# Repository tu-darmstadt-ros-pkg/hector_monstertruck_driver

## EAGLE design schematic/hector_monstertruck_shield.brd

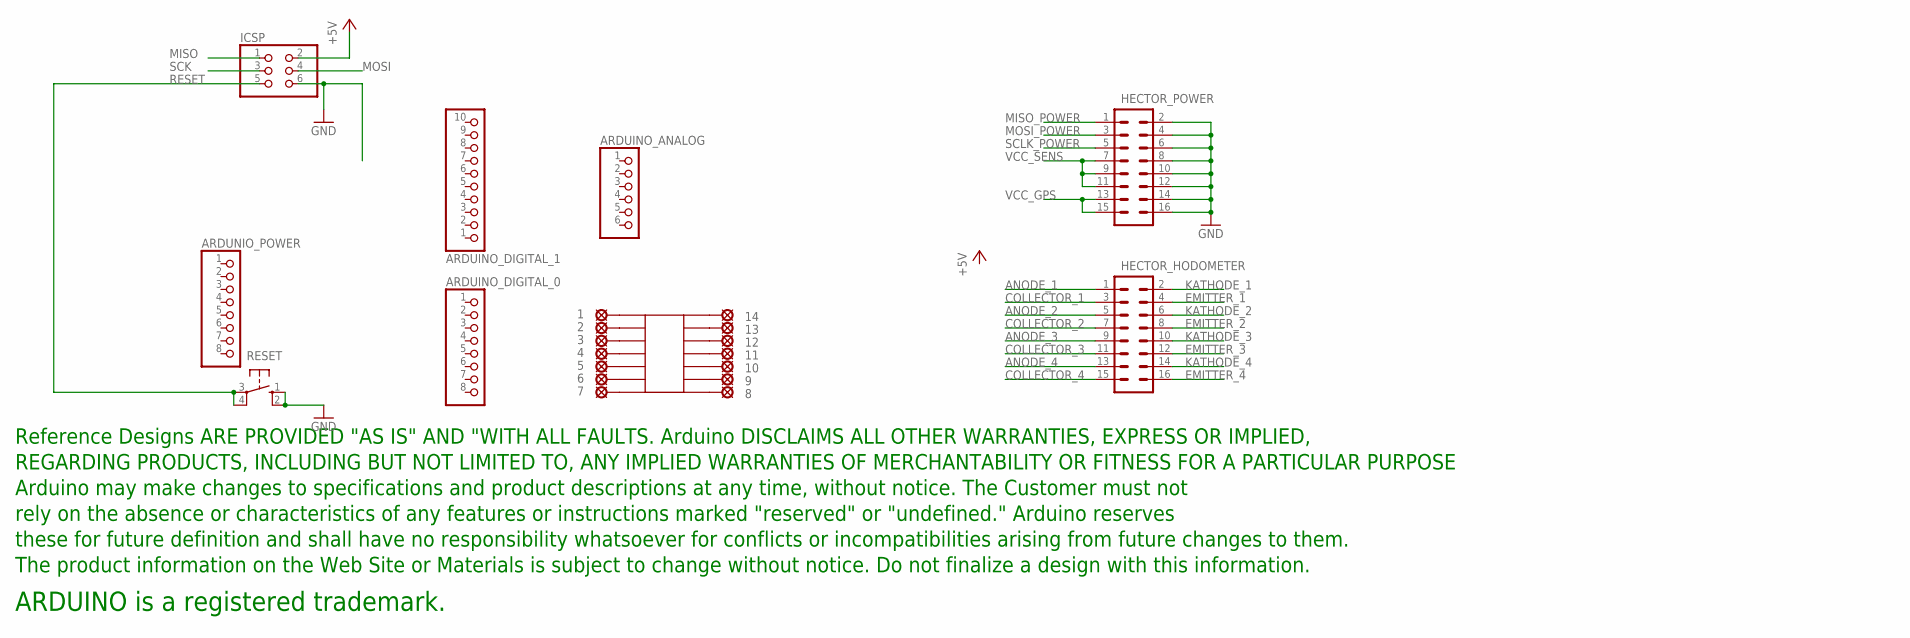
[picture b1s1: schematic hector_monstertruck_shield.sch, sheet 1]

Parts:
1, 2, 3, 4, 5, 6, 7, 8, 9, 10, 11, 12, 13, 14: LSP10
ARDUINO_ANALOG: PINHD-1X6; 1X06
ARDUINO_DIGITAL_0: PINHD-1X8TH; 1X08-TH
ARDUINO_DIGITAL_1: PINHD-1X10TH; 1X10-TH
ARDUNIO_POWER: PINHD-1X8TH; 1X08-TH
HECTOR_HODOMETER: M08X2; 2X8
HECTOR_POWER: M08X2; 2X8
IC2: SMD-14; SO-14NMW
ICSP: PINHD-2X3; 2X03
RESET: 10-XX; B3F-10XX
U$1: DISCLAIMER

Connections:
+5V: ICSP.2; also elsewhere on the board
ANODE_1: HECTOR_HODOMETER.1
ANODE_2: HECTOR_HODOMETER.5
ANODE_3: HECTOR_HODOMETER.9
ANODE_4: HECTOR_HODOMETER.13
COLLECTOR_1: HECTOR_HODOMETER.3
COLLECTOR_2: HECTOR_HODOMETER.7
COLLECTOR_3: HECTOR_HODOMETER.11
COLLECTOR_4: HECTOR_HODOMETER.15
EMITTER_1: HECTOR_HODOMETER.4
EMITTER_2: HECTOR_HODOMETER.8
EMITTER_3: HECTOR_HODOMETER.12
EMITTER_4: HECTOR_HODOMETER.16
GND: HECTOR_POWER.2, HECTOR_POWER.4, HECTOR_POWER.6, HECTOR_POWER.8, HECTOR_POWER.10, HECTOR_POWER.12, HECTOR_POWER.14, HECTOR_POWER.16, ICSP.6, RESET.1 (S), RESET.2 (S1); also elsewhere on the board
KATHODE_1: HECTOR_HODOMETER.2
KATHODE_2: HECTOR_HODOMETER.6
KATHODE_3: HECTOR_HODOMETER.10
KATHODE_4: HECTOR_HODOMETER.14
MISO: ICSP.1
MISO_POWER: HECTOR_POWER.1
MOSI: ICSP.4
MOSI_POWER: HECTOR_POWER.3
unnamed: 14.MP, IC2.P$14
unnamed: 13.MP, IC2.P$13
unnamed: 12.MP, IC2.P$12
unnamed: 11.MP, IC2.P$11
unnamed: 10.MP, IC2.P$10
unnamed: 9.MP, IC2.P$9
unnamed: 8.MP, IC2.P$8
unnamed: 7.MP, IC2.P$7
unnamed: 6.MP, IC2.P$6
unnamed: 5.MP, IC2.P$5
unnamed: 3.MP, IC2.P$3
unnamed: 2.MP, IC2.P$2
unnamed: 1.MP, IC2.P$1
unnamed: 4.MP, IC2.P$4
RESET: ICSP.5, RESET.3, RESET.4 (P1)
SCK: ICSP.3
SCLK_POWER: HECTOR_POWER.5
VCC_GPS: HECTOR_POWER.13, HECTOR_POWER.15
VCC_SENS: HECTOR_POWER.7, HECTOR_POWER.9, HECTOR_POWER.11

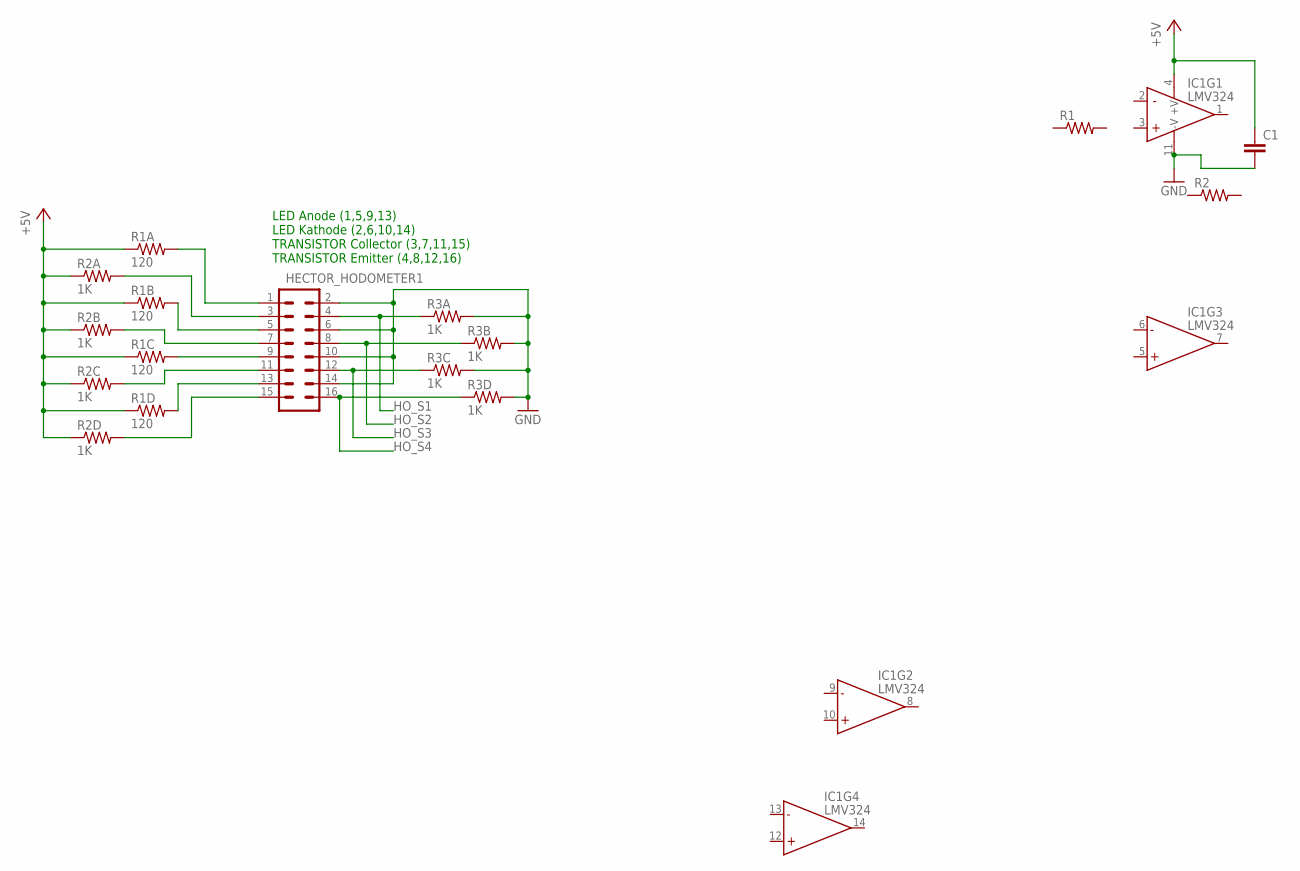
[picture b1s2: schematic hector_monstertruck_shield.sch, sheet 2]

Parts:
C1: CAPPTH; CAP-PTH-SMALL
HECTOR_HODOMETER1: M08X2; 2X8
IC1: LMV324; SO014
R1, R2: RESISTORPTH-1/4W; AXIAL-0.4
R1A, R1B, R1C, R1D: 120; AXIAL-0.4
R2A, R2B, R2C, R2D, R3A, R3B, R3C, R3D: 1K; AXIAL-0.4

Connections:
+5V: C1.1, IC1.4 (+V), R1A.P$1 (1), R1B.P$1 (1), R1C.P$1 (1), R1D.P$1 (1), R2A.P$1 (1), R2B.P$1 (1), R2C.P$1 (1), R2D.P$1 (1); also elsewhere on the board
AN_1: HECTOR_HODOMETER1.1, R1A.P$2 (2)
AN_2: HECTOR_HODOMETER1.5, R1B.P$2 (2)
AN_3: HECTOR_HODOMETER1.9, R1C.P$2 (2)
AN_4: HECTOR_HODOMETER1.13, R1D.P$2 (2)
CO_1: HECTOR_HODOMETER1.3, R2A.P$2 (2)
CO_2: HECTOR_HODOMETER1.7, R2B.P$2 (2)
CO_3: HECTOR_HODOMETER1.11, R2C.P$2 (2)
CO_4: HECTOR_HODOMETER1.15, R2D.P$2 (2)
GND: C1.2, HECTOR_HODOMETER1.2, HECTOR_HODOMETER1.6, HECTOR_HODOMETER1.10, HECTOR_HODOMETER1.14, IC1.11 (-V), R3A.P$2 (2), R3B.P$2 (2), R3C.P$2 (2), R3D.P$2 (2); also elsewhere on the board
HO_S1: HECTOR_HODOMETER1.4, R3A.P$1 (1)
HO_S2: HECTOR_HODOMETER1.8, R3B.P$1 (1)
HO_S3: HECTOR_HODOMETER1.12, R3C.P$1 (1)
HO_S4: HECTOR_HODOMETER1.16, R3D.P$1 (1)

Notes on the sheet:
LED Anode (1,5,9,13) LED Kathode (2,6,10,14) TRANSISTOR Collector (3,7,11,15) TRANSISTOR Emitter (4,8,12,16)

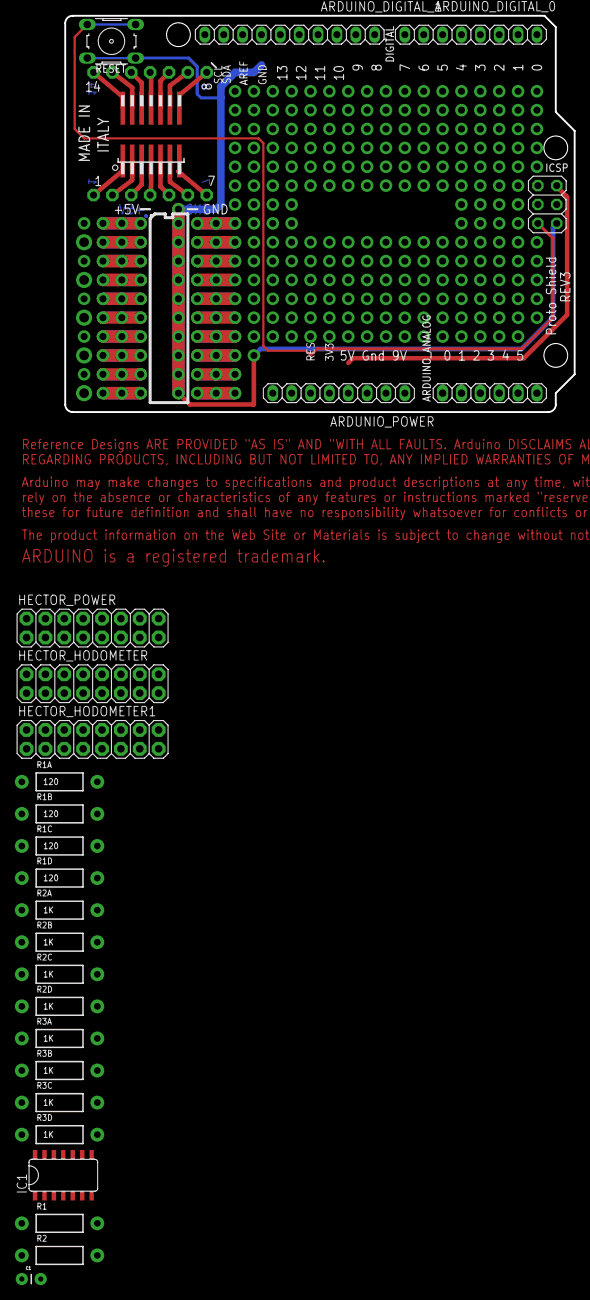
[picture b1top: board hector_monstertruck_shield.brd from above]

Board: 2 copper layers, 68.6 x 53.3 mm, 41 parts (0 on the bottom side), 31 nets.

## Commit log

2016-02-01 Basic functionality for serial communication
2016-02-03 Missing dependencie to monstertruck_msgs added
2016-02-05 Added files for arduino mega software
2016-02-05 * Excluded arduino files * Message comunication working so far * Parameter set for current setup
2016-02-05 Message output for imu and odometry
2016-02-10 Arduino.ino added
2016-02-11 Moved to rosserial and added schematics
2016-03-03 IMU handling async waiting
2016-03-18 Servo Command Callback added
2016-03-21 temp fix for defect wheel odom 2
2016-03-24 removed fake for rad2

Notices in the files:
parts and their libraries:
SparkFun-Connectors: Licensing: Creative Commons ShareAlike 4.0 International - https://creativecommons.org/licenses/by-sa/4.0
